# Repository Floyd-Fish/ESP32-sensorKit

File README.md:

# ESP32-sensorKit

<center>

</center>

I made this project for test only...  
Also I'm preparing for the next generation "End-World-Kit",which means End-World-Kit V2.0.  

## Progress
- Start Project --- 2020.3.5  
- Complete schematic design --- 2020.2.6  
- Complete PCB layout --- 2020.3.7  
- To be continued...

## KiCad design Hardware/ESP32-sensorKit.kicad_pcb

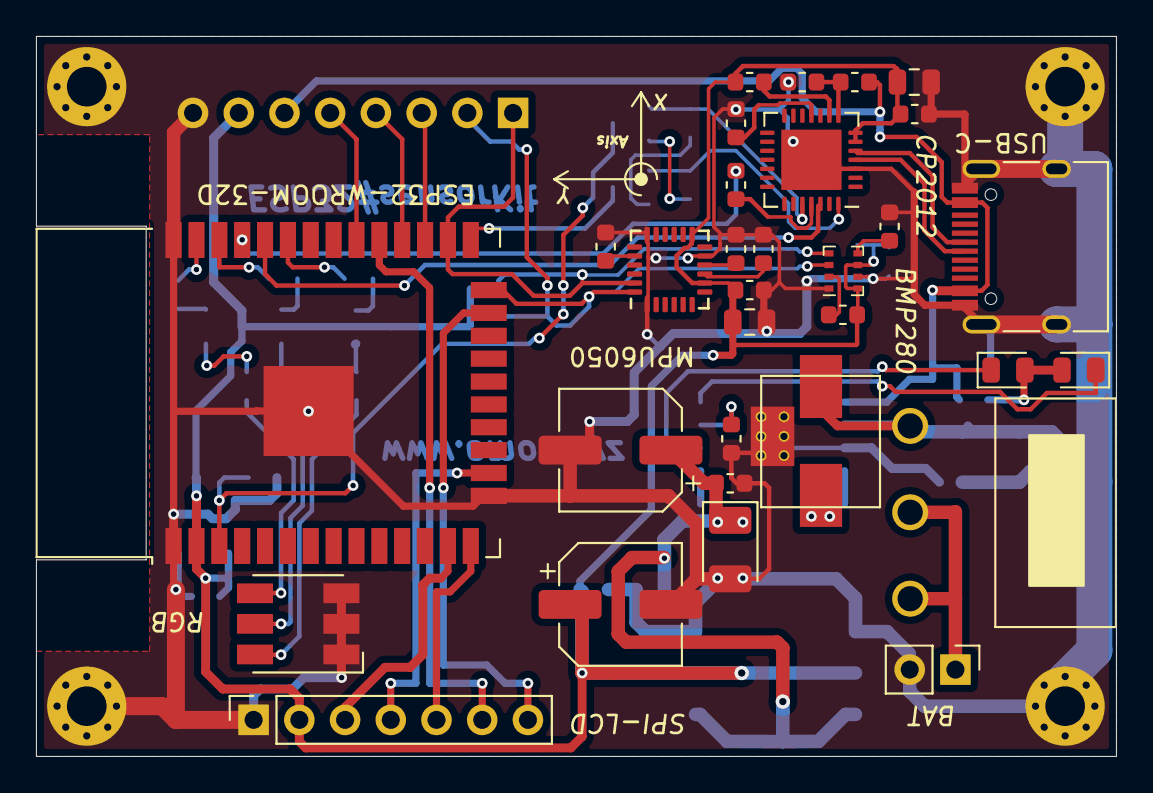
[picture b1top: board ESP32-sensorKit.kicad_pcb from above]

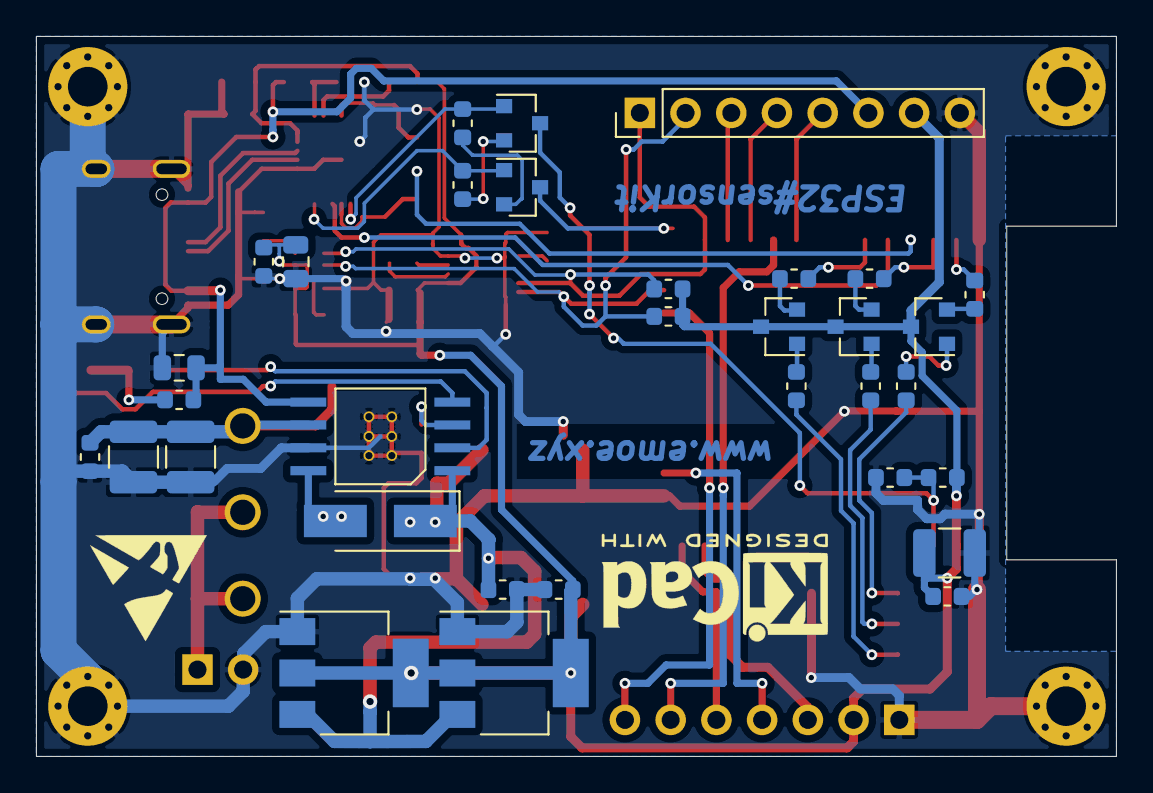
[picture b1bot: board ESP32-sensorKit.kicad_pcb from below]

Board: 2 copper layers, 60.0 x 40.0 mm, 68 parts (33 on the bottom side), 52 nets.

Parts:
BAT1: BAT Conn.; PinHeader_1x02_P2.54mm_Vertical
C1, C21: 220uF; CP_Elec_6.3x5.4
C2, C3, C6, C7, C9, C11, C13, C14, C16, C19: 104; C_0603_1608Metric
C4, C5, C8: 475; C_0805_2012Metric
C10: 222; C_0603_1608Metric
C12: 105; C_0805_2012Metric
C15, C17, C18: 22uF; C_1210_3225Metric
C20: 47uF; CP_EIA-3528-15_AVX-H_Pad1.50x2.35mm_HandSolder
D1: LED_RGB; LED_RGB_5050-6
D2: LED_G; D_0805_2012Metric
D3: LED_R; D_0805_2012Metric
D4: D_Schottky; D_SMA_Handsoldering
DIS_PORT1: DISPLAY; PinSocket_1x07_P2.54mm_Vertical
Extension-Pack1: Conn_01x08; PinHeader_1x08_P2.54mm_Vertical
H1, H2, H3, H4: PAD; MountingHole_2.2mm_M2_Pad_Via
L1: 10uH; 06030
P1: USB_C_Plug_USB2.0; USB_C_Receptacle_HRO_TYPE-C-31-M-12
PoweSwitch1: BAT Switch; SS12D06
Q1, Q2, Q3, Q4, Q5: S8050; SOT-23
R1, R17: 2k; R_0603_1608Metric
R2, R3, R4, R5, R6, R7, R15: 1k; R_0603_1608Metric
R8, R9, R10, R13, R14: 10k; R_0603_1608Metric
R11: 47k; R_0603_1608Metric
R12: 22k; R_0603_1608Metric
R16: 10k(NC); R_0603_1608Metric
R18: 10K; R_0603_1608Metric
R19: 470; R_0603_1608Metric
R20, R21: 4.7k; R_0603_1608Metric
U1, U2: AMS1117-3.3; SOT-223-3_TabPin2
U3: ESP32-WROOM-32D; ESP32-WROOM-32
U4: MPU-6050; InvenSense_QFN-24_4x4mm_P0.5mm
U5: BMP280; Bosch_LGA-8_2x2.5mm_P0.65mm_ClockwisePinNumbering
U6: CP2102N-A01; QFN-28-1EP_5x5mm_P0.5mm_EP3.35x3.35mm
U7: TP5400; ESOP-8

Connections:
/D+: P1.A6, U6.4
/D-: P1.A7, U6.5
/DTR: Q5.1, R13.2, U6.28
/EN: C14.1, Q4.3, R18.2, U3.3
/IO0: Q5.3, U3.25
/IO2_SDA: Extension-Pack1.2, R20.1, U3.24, U4.24, U5.3
/IO4_SCL: Extension-Pack1.1, R21.1, U3.26, U4.23, U5.4
/IO5_DC: DIS_PORT1.6, U3.29
/IO12_RES: DIS_PORT1.5, U3.14
/IO13_HSPI_DATA: DIS_PORT1.4, U3.16
/IO14_HSPI_CLK: DIS_PORT1.3, U3.13
/IO15_HSPI_CS0: DIS_PORT1.7, U3.23
/IO16_U2RXD: Extension-Pack1.3, U3.27
/IO17_U2TXD: Extension-Pack1.4, U3.28
/IO18: Extension-Pack1.5, U3.30
/IO21: R5.1, U3.33
/IO22: R6.1, U3.36
/IO23: R7.1, U3.37
/RTS: Q4.1, R14.2, U6.24
/RXD: R19.1, U3.35
/TXD: U3.34, U6.26
GND: BAT1.2, C1.2, C2.2, C3.2, C4.2, C5.2, C6.2, C7.2, C8.2, C9.1, C10.1, C11.1, C12.1, C13.2, C14.2, C15.2, C16.2, C17.2, C18.2, C19.2, C20.2, C21.2, D1.1, D1.2, D1.3, DIS_PORT1.1, Extension-Pack1.8, H1.1, H2.1, H3.1, H4.1, P1.A1, P1.A12, P1.B1, P1.B12, P1.S1, R8.1, R10.1, R11.1, R16.2, R17.1, U1.1, U2.1, U3.1, U3.15, U3.38, U3.39, U4.1, U4.11, U4.18, U5.1, U5.7, U6.3, U6.29, U7.7, U7.9, U7.10
unnamed: BAT1.1, PoweSwitch1.2, PoweSwitch1.3
unnamed: C1.1, C2.1, C19.1, C20.1, D4.1, U1.3, U2.3, U7.1
unnamed: C9.2, U4.10
unnamed: C10.2, U4.20
unnamed: D1.4, R4.2
unnamed: D1.5, R3.2
unnamed: D1.6, R2.2
unnamed: D2.1, U7.4
unnamed: D2.2, D3.2, R15.1
unnamed: D3.1, U7.2
unnamed: D4.2, L1.1, U7.8
unnamed: Q1.1, R2.1
unnamed: Q1.2, R5.2
unnamed: Q2.1, R3.1
unnamed: Q2.2, R6.2
unnamed: Q3.1, R4.1
unnamed: Q3.2, R7.2
unnamed: Q4.2, R13.1
unnamed: Q5.2, R14.1
unnamed: R1.2, U6.9
unnamed: R8.2, U4.9
unnamed: R9.1, U5.2
unnamed: R10.2, U5.5
unnamed: R11.2, R12.2, U6.8
unnamed: R16.1, U6.11
unnamed: R17.2, U7.3
unnamed: R19.2, U6.25
VBUS: C5.1, Extension-Pack1.6, P1.A4, P1.A9, P1.B4, P1.B9, R12.1, R15.2, U7.5
VCC: C3.1, C4.1, C6.1, C7.1, C8.1, C11.2, C12.2, C13.1, C15.1, C21.1, DIS_PORT1.2, Extension-Pack1.7, Q1.3, Q2.3, Q3.3, R1.1, R9.2, R18.1, R20.2, R21.2, U1.2, U2.2, U3.2, U4.8, U4.13, U5.6, U5.8, U6.6, U6.7
VPP: C16.1, C17.1, C18.1, L1.2, PoweSwitch1.1, U7.6

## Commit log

2020-03-10 Fix PCB bugs
2020-03-24 Update PCB gerber
